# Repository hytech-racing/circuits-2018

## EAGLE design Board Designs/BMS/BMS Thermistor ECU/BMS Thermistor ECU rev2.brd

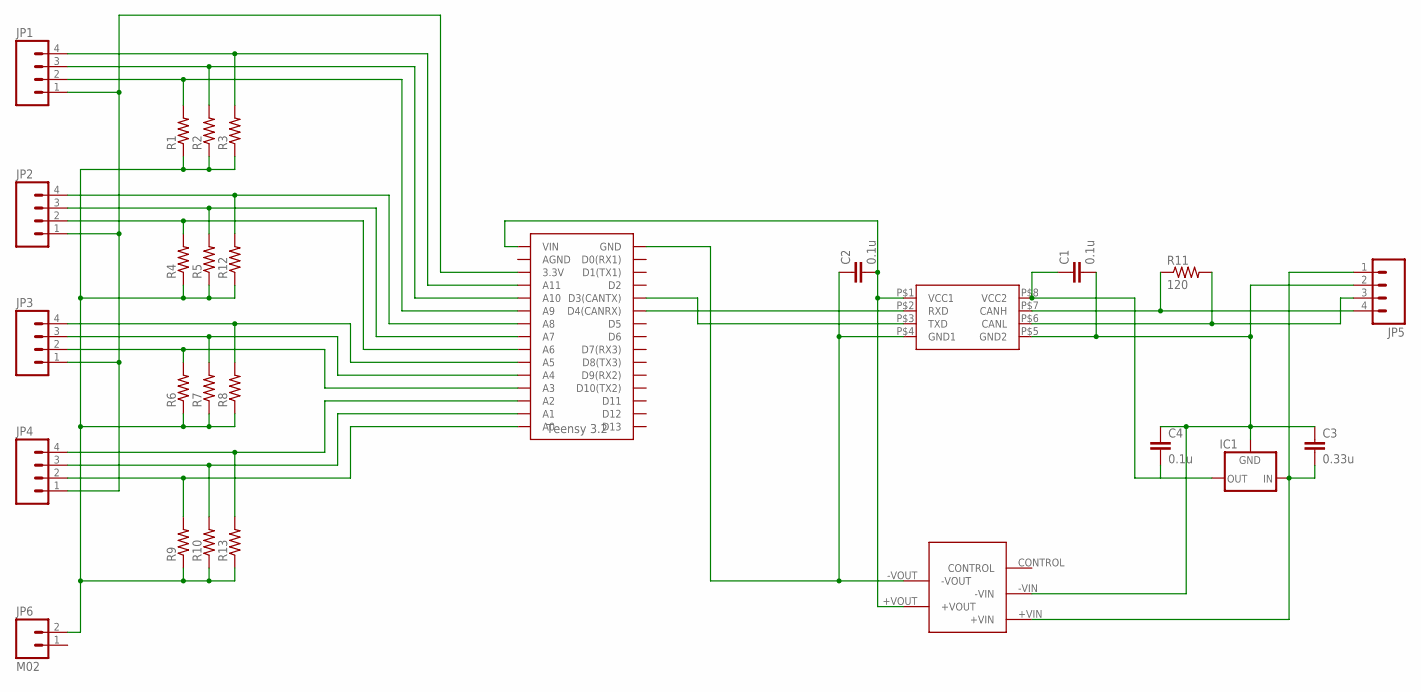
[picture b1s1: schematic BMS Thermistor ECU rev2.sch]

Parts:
C1, C2, C4: 0.1u; 0805
C3: 0.33u; 0805
IC1: 5VREG_L7805SPACED; TO-220-SPACED
JP1, JP2, JP3, JP4, JP5: M04; 1X04
JP6: M02; 1X02
R1, R2, R3, R4, R5, R6, R7, R8, R9, R10, R12, R13: RESISTOR0805-RES; 0805
R11: 120; 0805
U$1: TEENSY_3.2_12ANALOG
U$2: ISO1050CAN; DUB8
U$3: NCS1S1205SC-12V-5VCONVERTER; DCDC-CONVERTER

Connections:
3.3V: JP1.1, JP2.1, JP3.1, JP4.1, U$1.3.3V
unnamed: C1.2, C3.1, C4.1, IC1.2 (GND), JP5.2, U$2.P$5 (GND2), U$3.-VIN
unnamed: JP3.3, R7.2, U$1.A4
unnamed: JP3.4, R8.2, U$1.A5
unnamed: C3.2, IC1.1 (IN), JP5.1, U$3.+VIN
unnamed: C1.1, C4.2, IC1.3 (OUT), U$2.P$8 (VCC2)
unnamed: JP5.4, R11.1, U$2.P$7 (CANH)
unnamed: JP5.3, R11.2, U$2.P$6 (CANL)
unnamed: U$1.D3(CANTX), U$2.P$3 (TXD)
unnamed: U$1.D4(CANRX), U$2.P$2 (RXD)
unnamed: C2.2, U$1.VIN, U$2.P$1 (VCC1), U$3.+VOUT
unnamed: C2.1, U$1.GND, U$2.P$4 (GND1), U$3.-VOUT
unnamed: JP2.4, R12.2, U$1.A8
unnamed: JP4.4, R13.2, U$1.A2
THERM1: JP1.2, R1.2, U$1.A9
THERM2: JP1.3, R2.2, U$1.A10
THERM3: JP1.4, R3.2, U$1.A11
THERM4: JP2.2, R4.2, U$1.A6
THERM5: JP2.3, R5.2, U$1.A7
THERM6: JP3.2, R6.2, U$1.A3
THERM9: JP4.2, R9.2, U$1.A0
THERM10: JP4.3, R10.2, U$1.A1
TS_GND: JP6.2, R1.1, R2.1, R3.1, R4.1, R5.1, R6.1, R7.1, R8.1, R9.1, R10.1, R12.1, R13.1

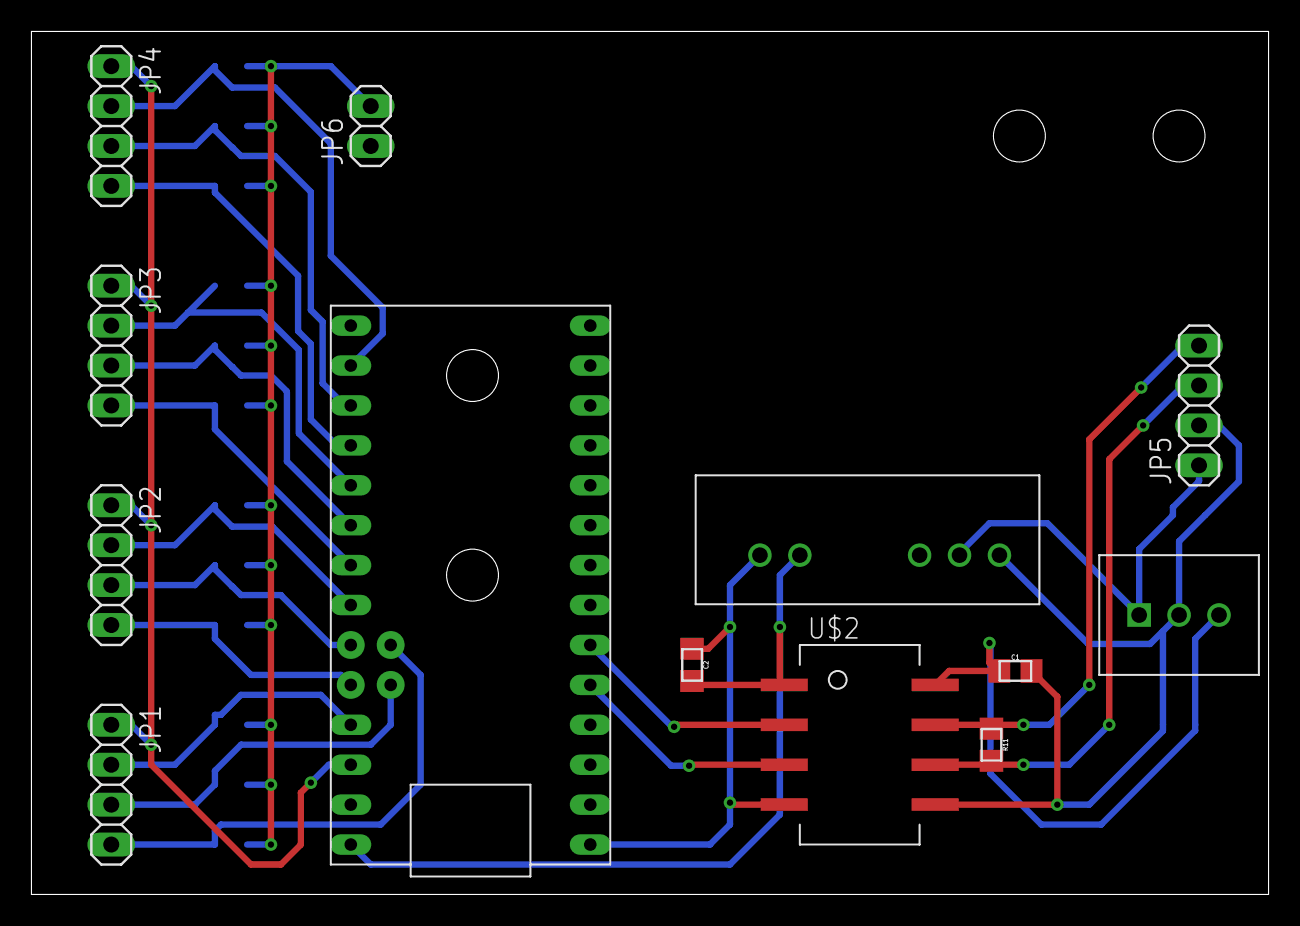
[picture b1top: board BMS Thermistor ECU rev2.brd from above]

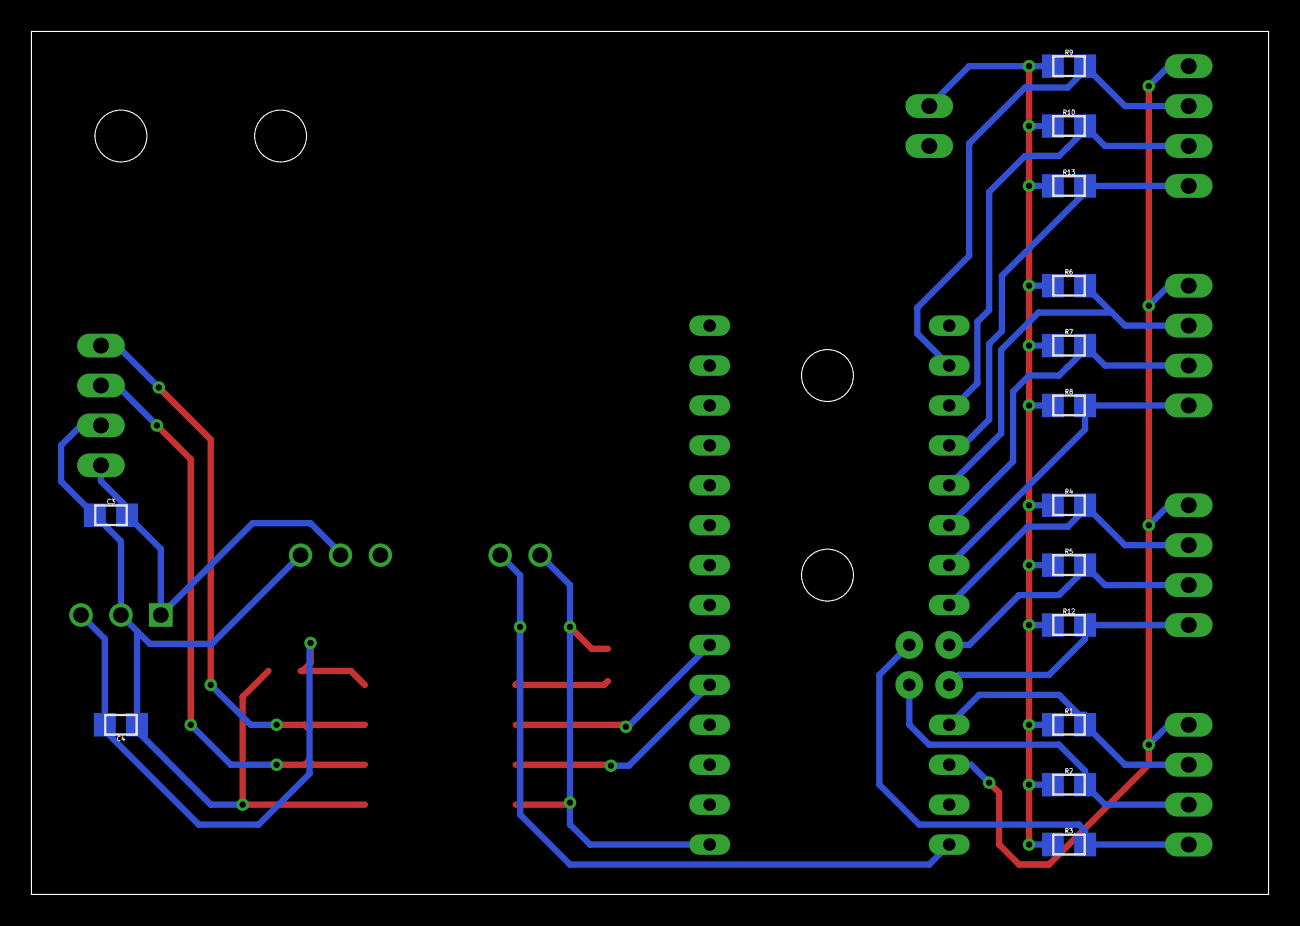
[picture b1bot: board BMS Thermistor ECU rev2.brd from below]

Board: 2 copper layers, 78.7 x 54.9 mm, 27 parts (14 on the bottom side), 23 nets.

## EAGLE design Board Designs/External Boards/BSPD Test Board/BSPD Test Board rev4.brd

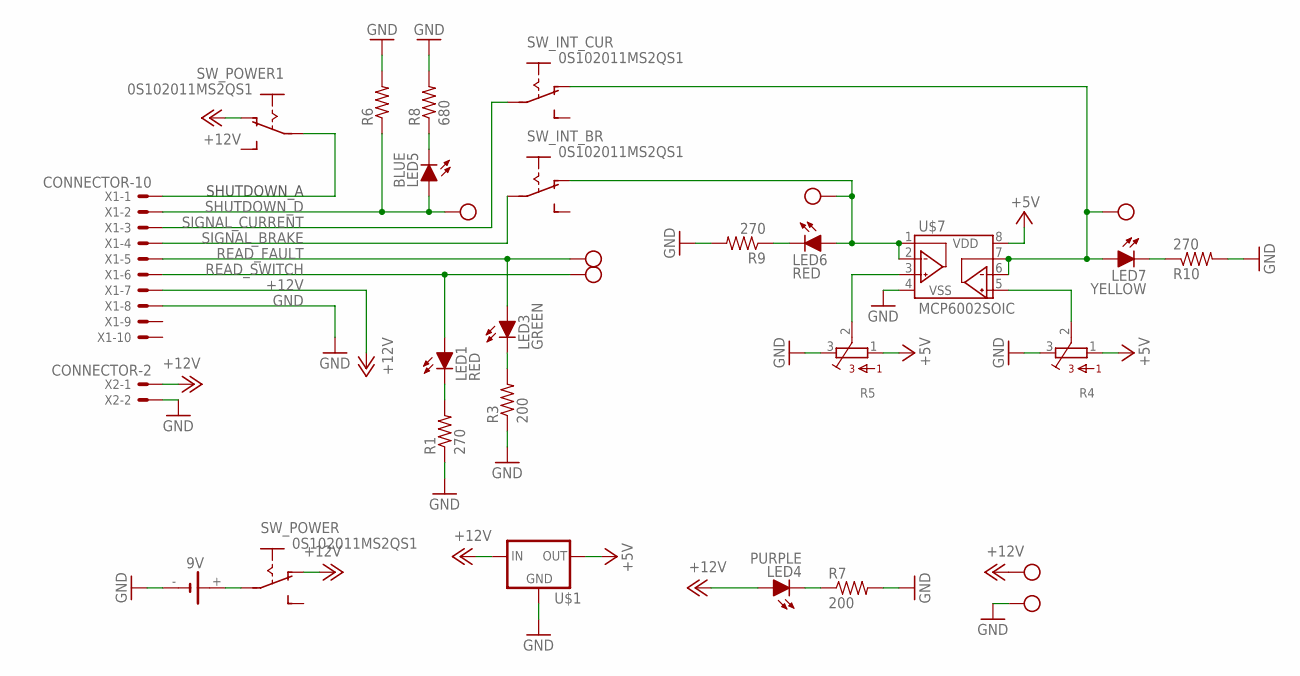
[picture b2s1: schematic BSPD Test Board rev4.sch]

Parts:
9V: 1291-79
LED1: RED; LED-5MM
LED3: GREEN; LED-5MM
LED4: PURPLE; LED-805
LED5: BLUE; LED-5MM
LED6: RED; LED-805
LED7: YELLOW; LED-805
R1, R9, R10: 270; 0805
R3, R7: 200; 0805
R4, R5: TRIMPOT_3296C; TRIMPOT_3296
R6: RESISTORPTH-1/2W; AXIAL-0.5
R8: 680; 0805
SW_INT_BR: 0S102011MS2QS1
SW_INT_CUR: 0S102011MS2QS1
SW_POWER, SW_POWER1: 0S102011MS2QS1
U$1: 5VREG_LM340-NLM340MPX-5.0/NOPB; SOT223
U$2, U$3, U$4, U$5, U$6, U$8, U$10: TEST_POINT
U$7: MCP6002SOIC; SOIC-08
X1: CONNECTOR-10; MINIFIT_5566-10
X2: CONNECTOR-2; MINIFIT_5566-2

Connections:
+5V: R4.1, R5.1, U$1.3 (OUT), U$7.8 (VDD)
+12V: LED4.A, SW_POWER.P$1 (O), SW_POWER1.P$1 (O), U$1.1 (IN), U$5.P$1, X1.7, X2.1
GND: 9V.-, R1.1, R3.1, R4.3, R5.3, R6.P$2 (2), R7.2, R8.2, R9.2, R10.2, U$1.2 (GND), U$1.4 (GND), U$6.P$1, U$7.4 (VSS), X1.8, X2.2
unnamed: LED1.K (C), R1.2
unnamed: LED3.K (C), R3.2
unnamed: R4.2, U$7.5 (VINB+)
unnamed: R5.2, U$7.3 (VINA+)
unnamed: 9V.+, SW_POWER.P$2
unnamed: LED4.C, R7.1
unnamed: LED6.A, SW_INT_BR.P$1 (O), U$3.P$1, U$7.1 (VOUTA), U$7.2 (VINA-)
unnamed: LED7.A, SW_INT_CUR.P$1 (O), U$2.P$1, U$7.6 (VINB-), U$7.7 (VOUTB)
unnamed: LED6.C, R9.1
unnamed: LED5.K (C), R8.1
unnamed: LED7.C, R10.1
unnamed: SW_POWER1.P$2, X1.1
READ_FAULT: LED3.A, U$8.P$1, X1.5
READ_SWITCH: LED1.A, U$10.P$1, X1.6
SHUTDOWN_D: LED5.A, R6.P$1 (1), U$4.P$1, X1.2
SIGNAL_BRAKE: SW_INT_BR.P$2, X1.4
SIGNAL_CURRENT: SW_INT_CUR.P$2, X1.3

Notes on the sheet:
SHUTDOWN_A

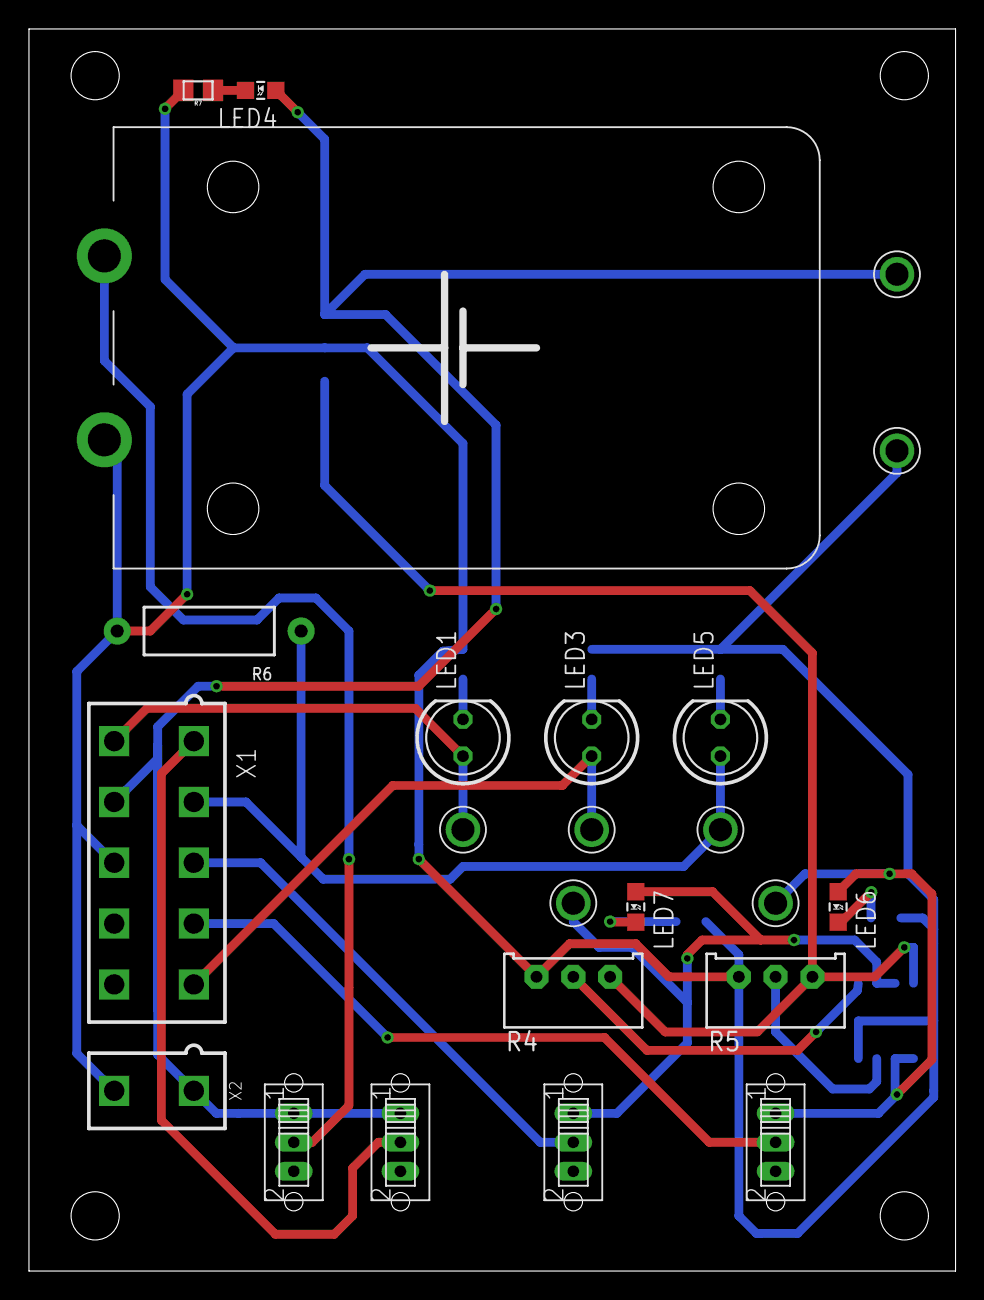
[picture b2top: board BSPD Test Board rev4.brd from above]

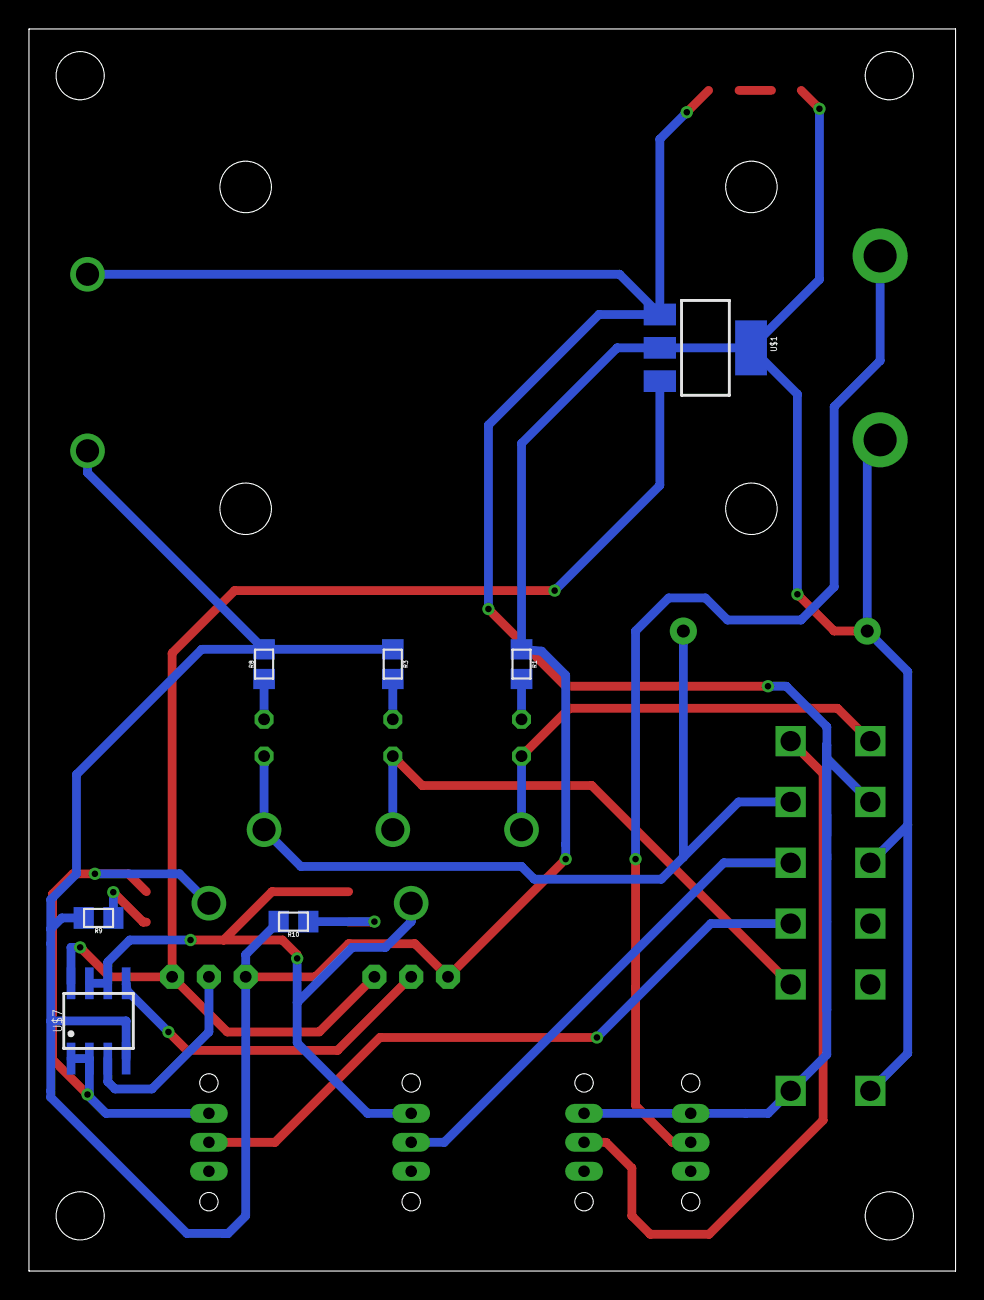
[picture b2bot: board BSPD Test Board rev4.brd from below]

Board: 2 copper layers, 64.0 x 85.8 mm, 31 parts (7 on the bottom side), 20 nets.

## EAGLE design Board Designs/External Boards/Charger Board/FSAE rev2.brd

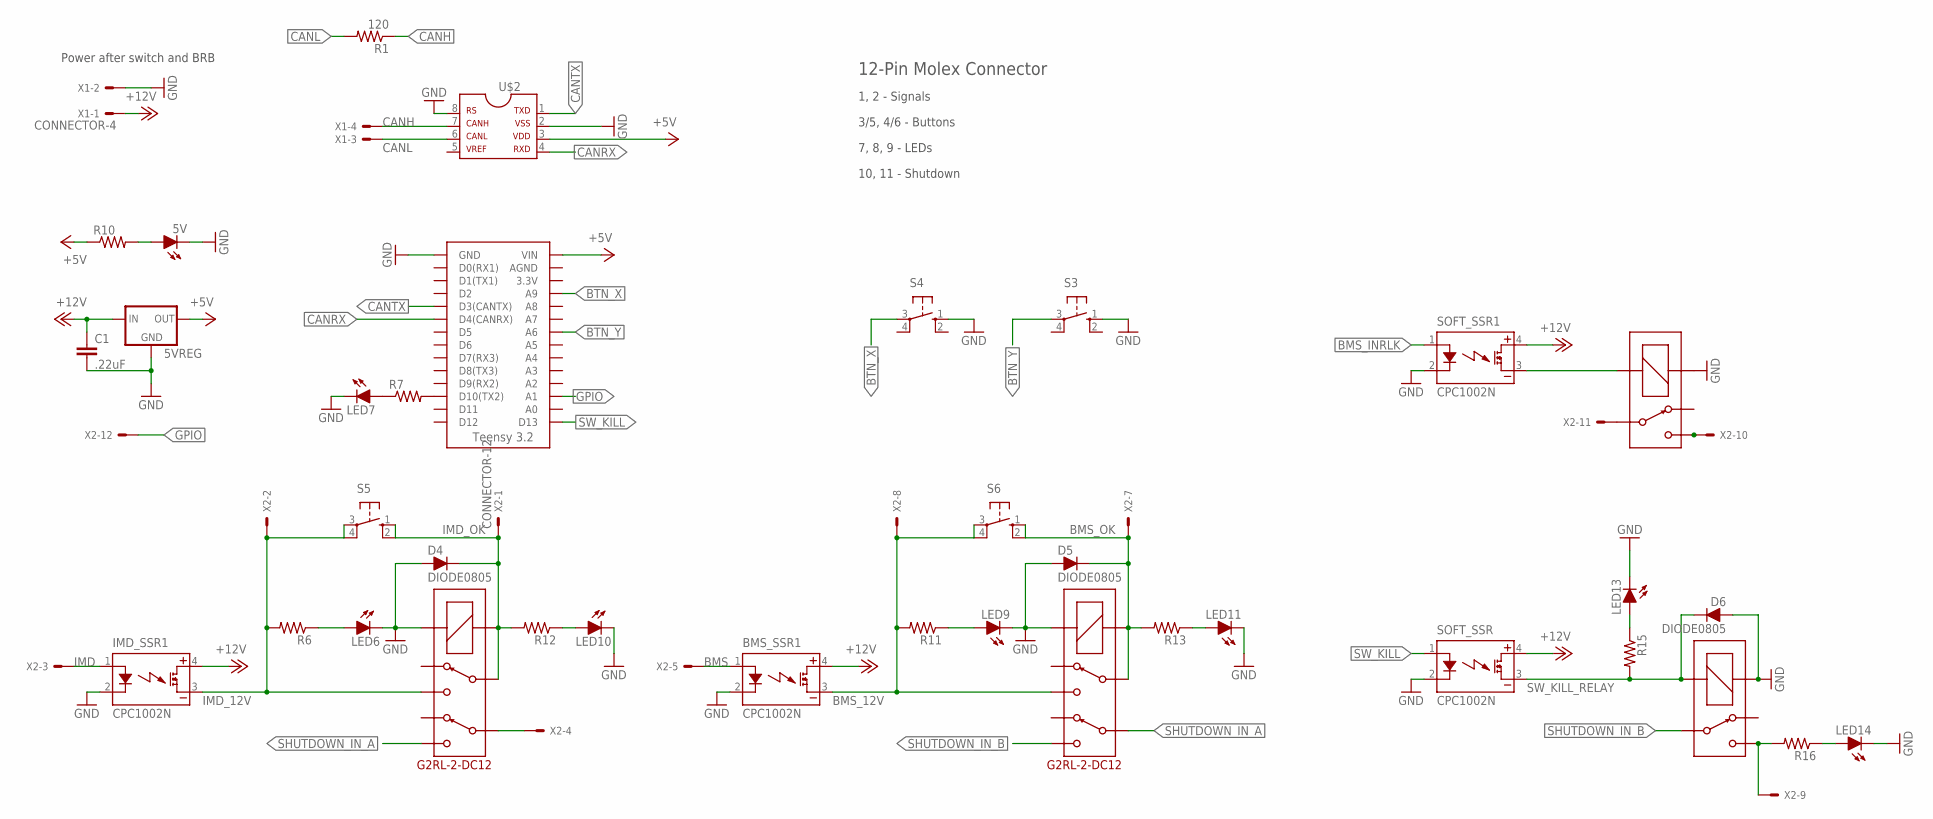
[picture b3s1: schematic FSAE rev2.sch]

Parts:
5V: LED-0805; LED-805
5VREG: 5VREG_LM340-NLM340MPX-5.0/NOPB; SOT223
BMS_SSR1: CPC1002N; SOP04
C1: .22uF; 0805
D4, D5, D6: DIODE0805; 0805_D
IMD_SSR1: CPC1002N; SOP04
LED6, LED7, LED9, LED10, LED11, LED13, LED14: LED-0805; LED-805
R1: 120; 0805
R6, R7, R10, R11, R12, R13, R15, R16: RESISTOR0805-RES; 0805
S3, S4, S5, S6: BTN_10-XX; B3F-10XX
SOFT_SSR, SOFT_SSR1: CPC1002N; SOP04
U$1: TEENSY_3.2_SIMPLE
U$2: MCP2551; SOIC-08
U$3, U$8: G5LE; ZF112
U$6, U$7: G2RL-2-DC12; G2RL-2
X1: CONNECTOR-4; MINIFIT_5566-4
X2: CONNECTOR-12; MINIFIT_5566-12

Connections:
+5V: 5VREG.3 (OUT), R10.1, U$1.VIN, U$2.3
+12V: 5VREG.1 (IN), BMS_SSR1.4 (DC+), C1.1, IMD_SSR1.4 (DC+), SOFT_SSR.4 (DC+), SOFT_SSR1.4 (DC+), X1.1
BMS: BMS_SSR1.1 (CONTROL+), X2.5
BMS_12V: BMS_SSR1.3 (DC-), R11.2, S6.3, S6.4 (P1), U$7.4, X2.8
BMS_INRLK: SOFT_SSR1.1 (CONTROL+)
BMS_OK: D5.C, R13.2, S6.1 (S), S6.2 (S1), U$7.3, U$7.COIL-, X2.7
BTN_X: S4.3, U$1.A9
BTN_Y: S3.3, U$1.A6
CANH: R1.1, U$2.7, X1.4
CANL: R1.2, U$2.6, X1.3
CANRX: U$1.D4(CANRX), U$2.4
CANTX: U$1.D3(CANTX), U$2.1
GND: 5V.C, 5VREG.2 (GND), 5VREG.4 (GND), BMS_SSR1.2 (CONTROL-), C1.2, D4.A, D5.A, D6.A, IMD_SSR1.2 (CONTROL-), LED6.C, LED7.C, LED9.C, LED10.C, LED11.C, LED13.C, LED14.C, S3.1 (S), S4.1 (S), SOFT_SSR.2 (CONTROL-), SOFT_SSR1.2 (CONTROL-), U$1.GND, U$2.2, U$2.8, U$3.1 (COIL+), U$6.COIL+, U$7.COIL+, U$8.1 (COIL+), X1.2
GPIO: U$1.A1, X2.12
IMD: IMD_SSR1.1 (CONTROL+), X2.3
IMD_12V: IMD_SSR1.3 (DC-), R6.2, S5.3, S5.4 (P1), U$6.4, X2.2
IMD_OK: D4.C, R12.2, S5.1 (S), S5.2 (S1), U$6.3, U$6.COIL-, X2.1
unnamed: SOFT_SSR1.3 (DC-), U$3.2 (COIL-)
unnamed: LED7.A, R7.1
unnamed: 5V.A, R10.2
unnamed: U$3.S, X2.6, X2.10
unnamed: LED6.A, R6.1
unnamed: LED9.A, R11.1
unnamed: LED10.A, R12.1
unnamed: U$3.P, X2.11
unnamed: R7.2, U$1.D10(TX2)
unnamed: LED11.A, R13.1
unnamed: LED14.A, R16.1
unnamed: LED13.A, R15.1
SHUTDOWN_IN: U$6.6, X2.4
SHUTDOWN_IN_A: U$6.5, U$7.6
SHUTDOWN_IN_B: U$7.5, U$8.P
SHUTDOWN_OUT: R16.2, U$8.S, X2.9
SW_KILL: SOFT_SSR.1 (CONTROL+), U$1.D13
SW_KILL_RELAY: D6.C, R15.2, SOFT_SSR.3 (DC-), U$8.2 (COIL-)

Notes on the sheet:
Power after switch and BRB
7, 8, 9 - LEDs
3/5, 4/6 - Buttons
1, 2 - Signals
10, 11 - Shutdown
12-Pin Molex Connector

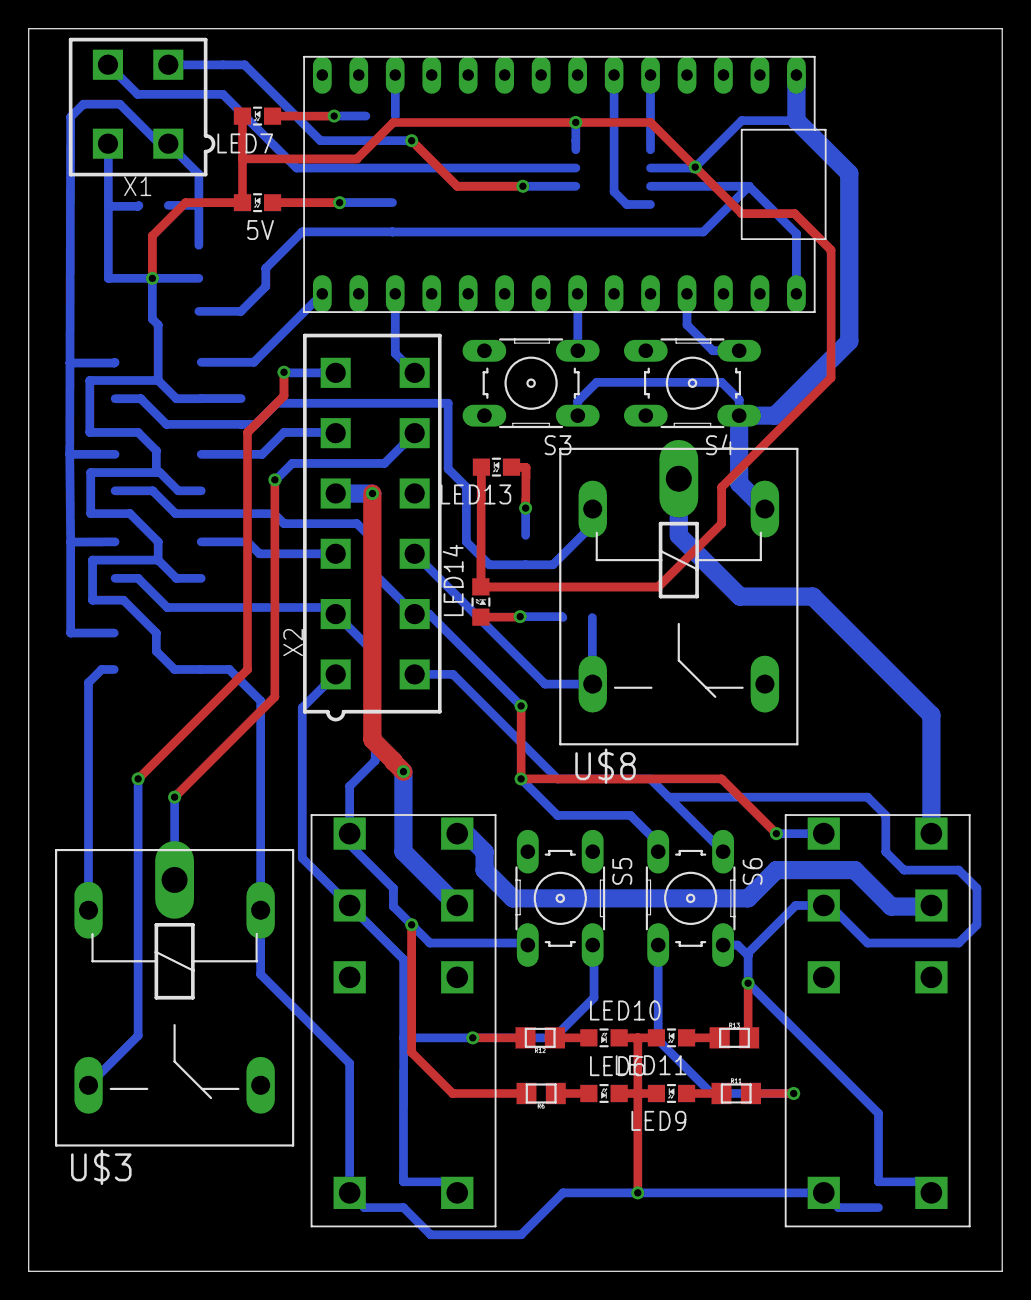
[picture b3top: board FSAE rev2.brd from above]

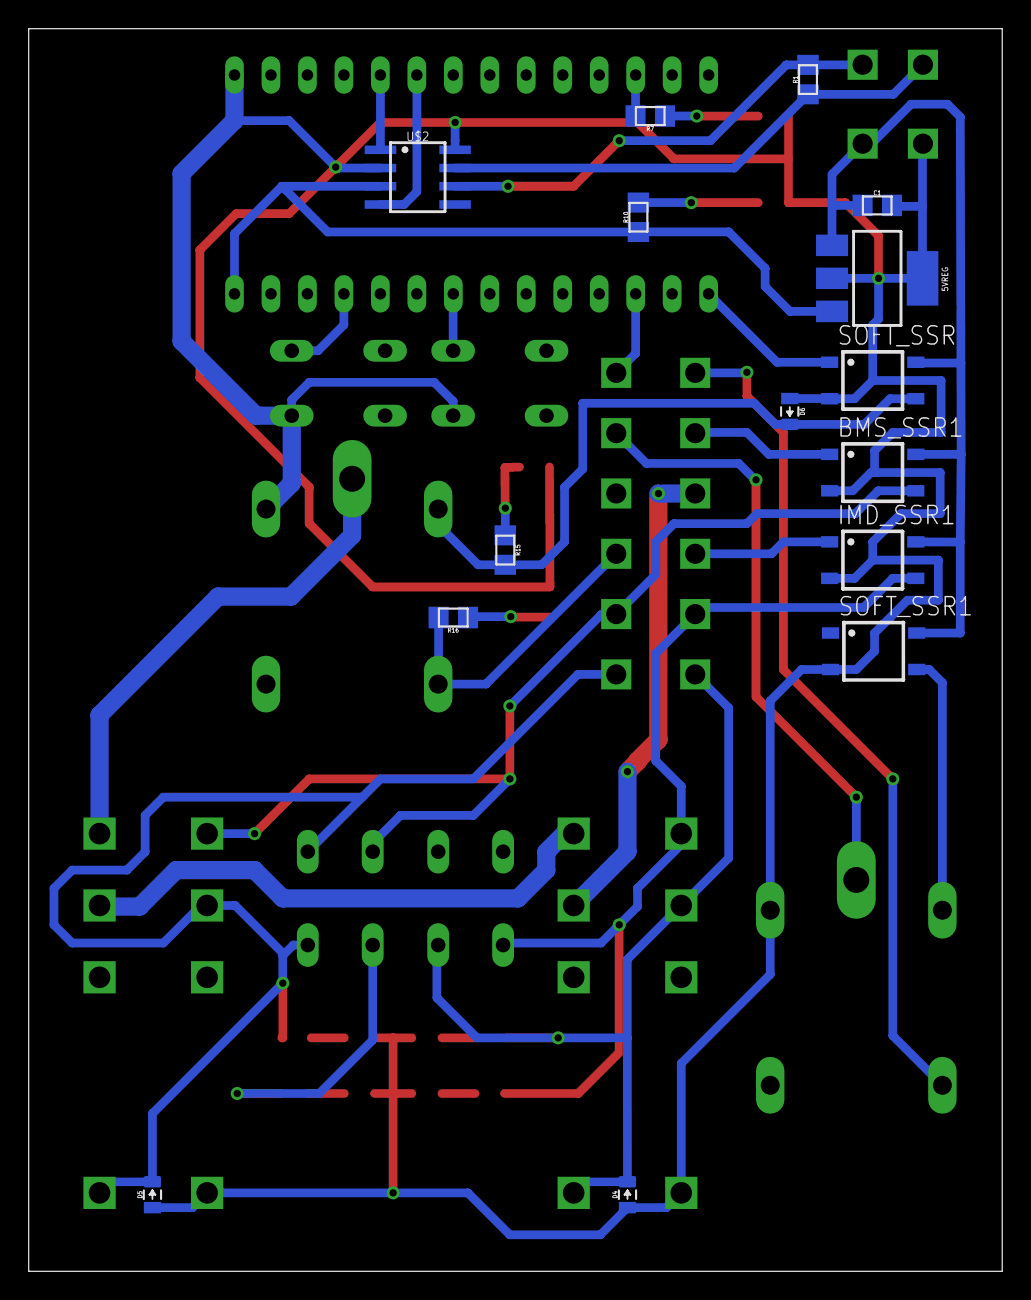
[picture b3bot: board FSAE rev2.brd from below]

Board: 2 copper layers, 67.8 x 86.5 mm, 38 parts (15 on the bottom side), 34 nets.

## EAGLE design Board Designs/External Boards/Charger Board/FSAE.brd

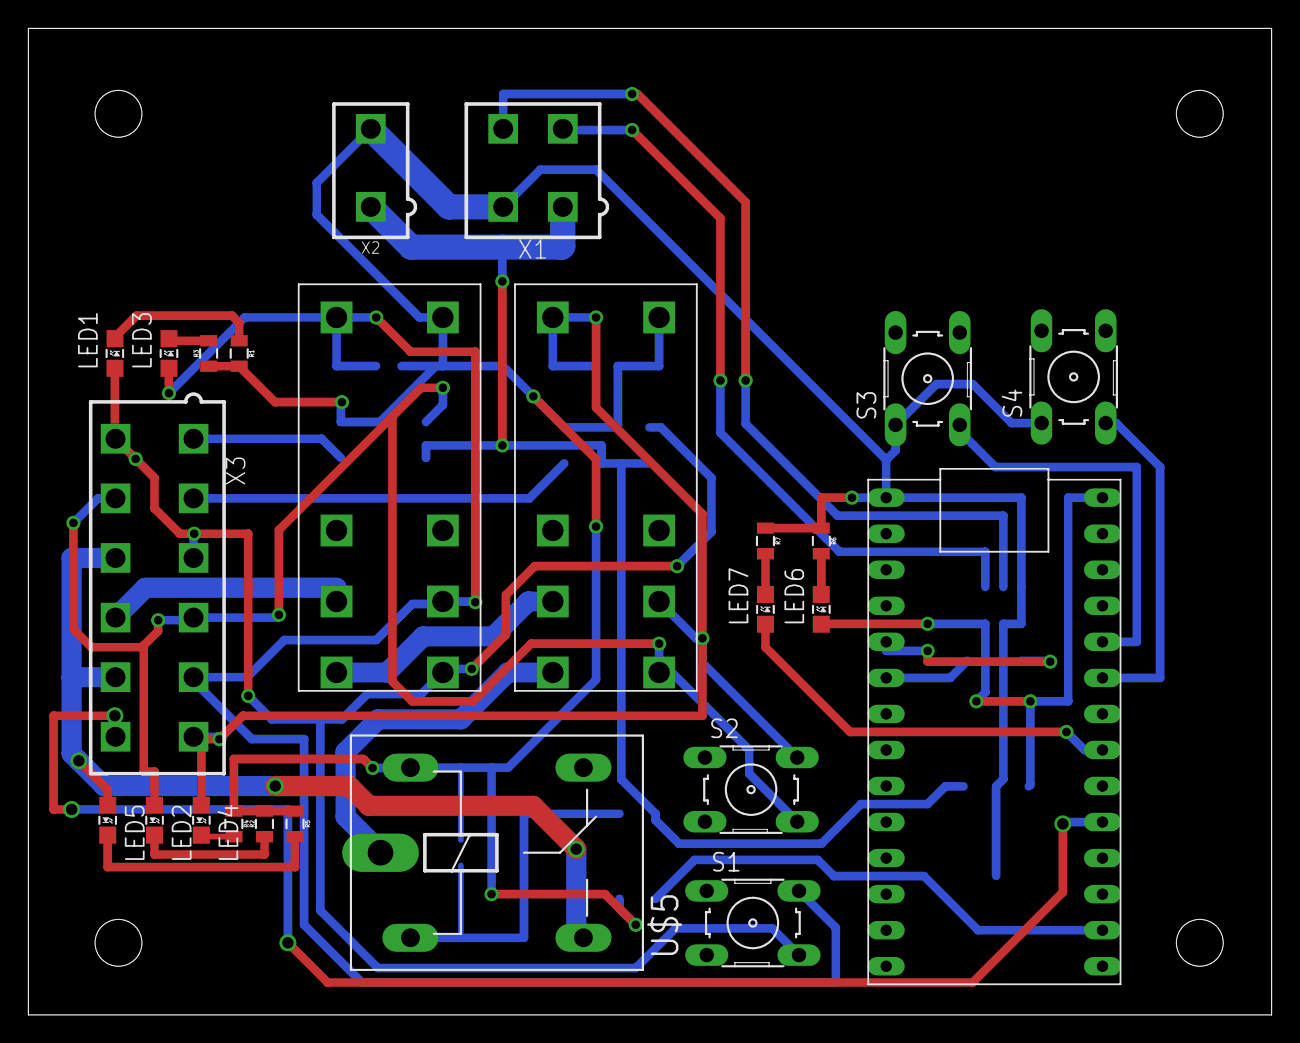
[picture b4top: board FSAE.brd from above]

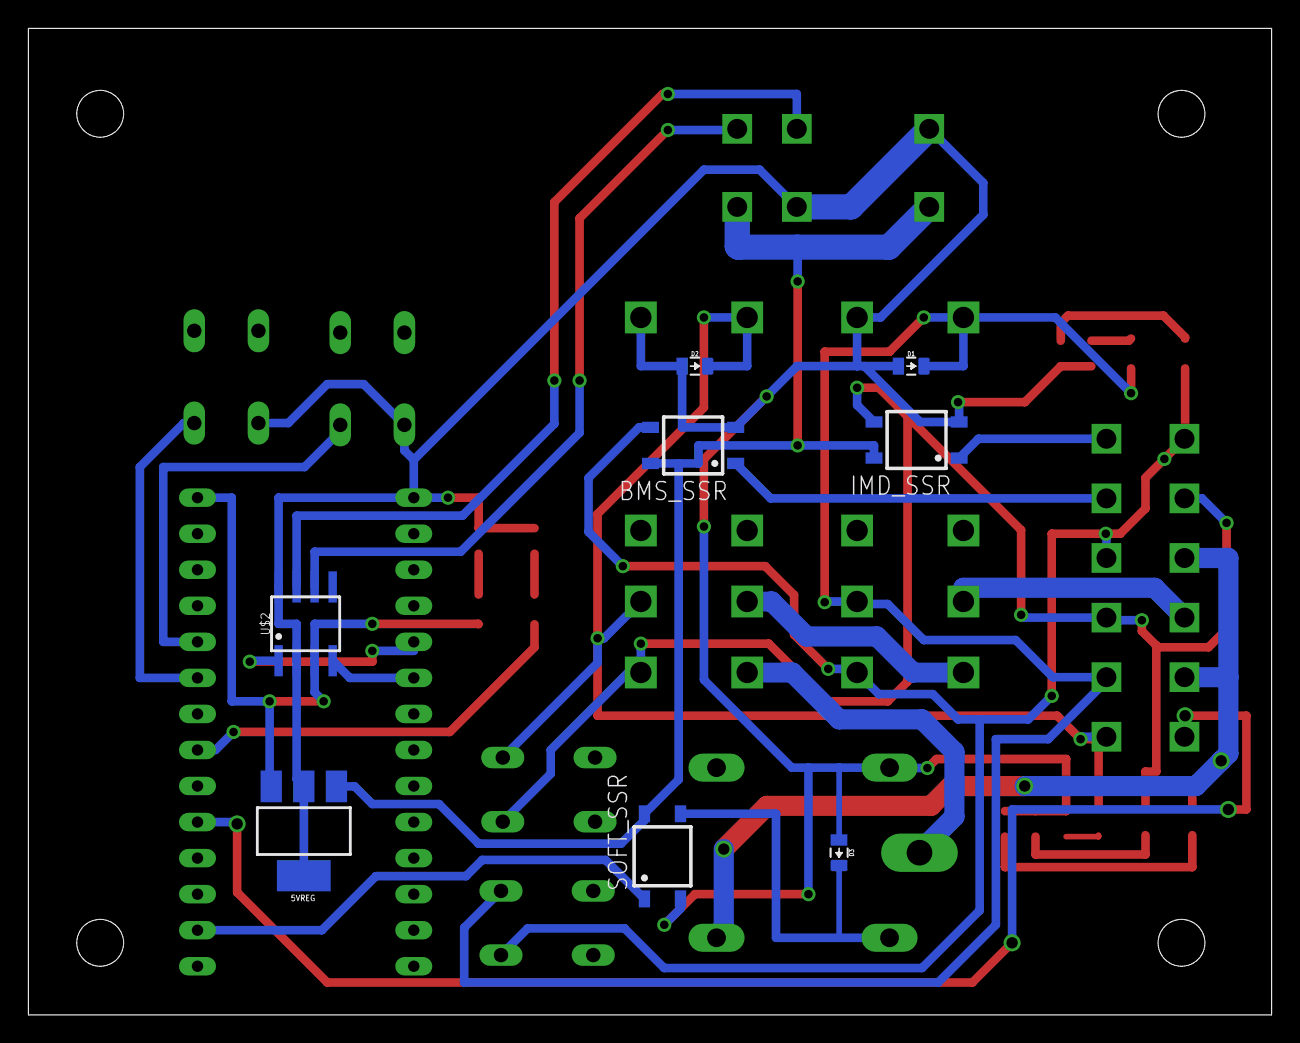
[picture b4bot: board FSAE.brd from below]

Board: 2 copper layers, 87.6 x 69.5 mm, 33 parts (8 on the bottom side), 30 nets.

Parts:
5VREG: SOT223
BMS_SSR: CPC1002N; SOP04
D1, D2, D3: DIODE0805; 0805_D
IMD_SSR: CPC1002N; SOP04
LED1, LED2, LED3, LED4, LED5, LED6, LED7: LED-805
R1, R2, R3, R4, R5, R6, R7: 0805
S1, S2, S3, S4: B3F-10XX
SOFT_SSR: CPC1002N; SOP04
U$1: TEENSY_3.2_SIMPLE
U$2: MCP2551; SOIC-08
U$3, U$4: G2RL-2-DC12; G2RL-2
U$5: G5LE; ZF112
X1: CONNECTOR-4; MINIFIT_5566-4
X2: CONNECTOR-2; MINIFIT_5566-2
X3: CONNECTOR-12; MINIFIT_5566-12

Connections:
+5V: 5VREG.3, LED6.A, U$1.VIN, U$2.3
+12V: 5VREG.1, BMS_SSR.4, IMD_SSR.4, SOFT_SSR.4, X1.1, X2.1
BMS: BMS_SSR.1, X3.2
BMS_LATCH: D2.C, LED4.A, S2.2, U$4.3, U$4.COIL-, X3.6
BMS_RELAY: IMD_SSR.3, LED2.A, S2.4, U$4.4, X3.4, X3.8
GND: 5VREG.2, 5VREG.4, BMS_SSR.2, D1.A, D2.A, D3.A, IMD_SSR.2, R1.2, R2.2, R3.1, R4.1, R5.1, R6.1, R7.1, S3.1, S4.1, SOFT_SSR.2, U$1.GND, U$2.2, U$2.8, U$3.COIL+, U$4.COIL+, U$5.1, X1.2, X2.2
GPIO: U$1.A3, X3.12
IMD: IMD_SSR.1, X3.1
IMD_LATCH: D1.C, LED3.A, S1.2, U$3.3, U$3.COIL-, X3.5
IMD_RELAY: BMS_SSR.3, LED1.A, S1.4, U$3.4, X3.3, X3.7
unnamed: U$3.5, U$4.6
unnamed: U$4.5, U$5.P
unnamed: U$1.D3(CANTX), U$2.1
unnamed: U$1.D4(CANRX), U$2.4
unnamed: U$2.6, X1.3
unnamed: U$2.7, X1.4
unnamed: LED6.C, R6.2
unnamed: S3.3, U$1.A8
unnamed: D3.C, SOFT_SSR.3, U$5.2
unnamed: LED7.C, R7.2
unnamed: LED7.A, U$1.A5
unnamed: S4.3, U$1.A7
unnamed: SOFT_SSR.1, U$1.A0
unnamed: LED2.C, R2.1
unnamed: LED1.C, R1.1
unnamed: LED3.C, R3.2
unnamed: LED4.C, R4.2
unnamed: LED5.C, R5.2
SHUTDOWN_IN: U$3.6, X3.10
SHUTDOWN_OUT: LED5.A, U$5.S, X3.9, X3.11

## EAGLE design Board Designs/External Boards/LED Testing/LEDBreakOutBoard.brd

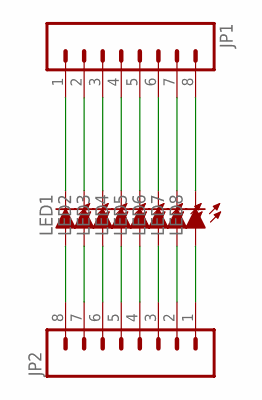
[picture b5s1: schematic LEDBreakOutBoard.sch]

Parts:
JP1, JP2: M08; 1X08
LED1, LED2, LED3, LED4, LED5, LED6, LED7, LED8: LED-0805; LED-805

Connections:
unnamed: JP1.1, LED1.C
unnamed: JP2.8, LED1.A
unnamed: JP2.7, LED2.A
unnamed: JP1.2, LED2.C
unnamed: JP2.6, LED3.A
unnamed: JP1.3, LED3.C
unnamed: JP2.5, LED4.A
unnamed: JP1.4, LED4.C
unnamed: JP1.5, LED5.C
unnamed: JP2.4, LED5.A
unnamed: JP2.3, LED6.A
unnamed: JP1.6, LED6.C
unnamed: JP1.7, LED7.C
unnamed: JP2.2, LED7.A
unnamed: JP2.1, LED8.A
unnamed: JP1.8, LED8.C

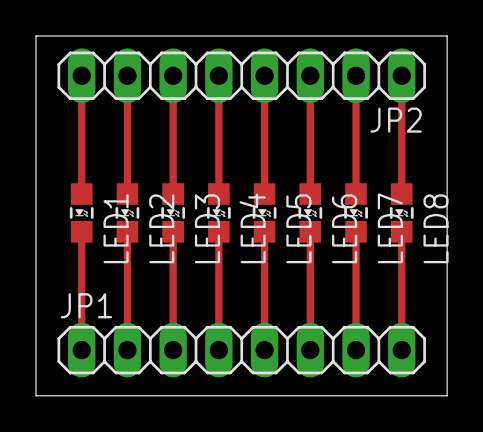
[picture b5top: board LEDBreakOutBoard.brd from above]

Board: 2 copper layers, 22.8 x 20.0 mm, 10 parts (0 on the bottom side), 16 nets.

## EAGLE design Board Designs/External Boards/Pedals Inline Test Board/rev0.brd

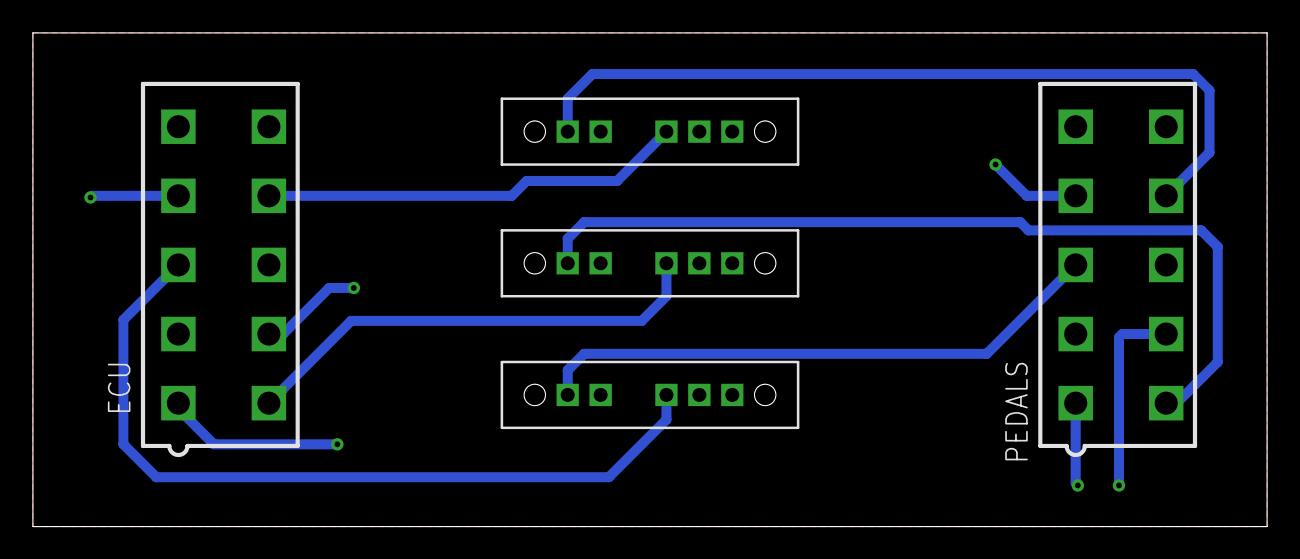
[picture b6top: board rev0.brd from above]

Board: 2 copper layers, 75.0 x 30.0 mm, 5 parts (0 on the bottom side), 8 nets.

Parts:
ECU: CONNECTOR-10; MINIFIT_5566-10
PEDALS: CONNECTOR-10; MINIFIT_5566-10
U$1, U$2, U$3: SS-14D0839-VG5PA

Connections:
+5V: ECU.1, ECU.4, ECU.7, PEDALS.1, PEDALS.4, PEDALS.7, U$1.4, U$2.4, U$3.4
GND: ECU.2, ECU.5, ECU.8, PEDALS.2, PEDALS.5, PEDALS.8, U$1.3, U$2.3, U$3.3
unnamed: ECU.9, U$1.COM
unnamed: ECU.6, U$2.COM
unnamed: ECU.3, U$3.COM
unnamed: PEDALS.9, U$1.1
unnamed: PEDALS.6, U$2.1
unnamed: PEDALS.3, U$3.1
